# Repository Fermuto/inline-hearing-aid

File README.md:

# inline-hearing-aid
In development.

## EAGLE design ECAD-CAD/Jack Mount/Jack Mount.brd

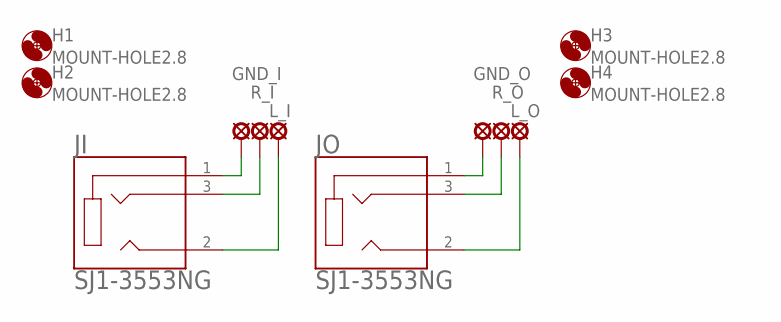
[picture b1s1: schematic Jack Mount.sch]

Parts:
GND_I: LSP10
GND_O: LSP10
H1, H2, H3, H4: MOUNT-HOLE2.8; 2,8
JI: SJ1-3553NG; CUI_SJ1-3553NG
JO: SJ1-3553NG; CUI_SJ1-3553NG
L_I: LSP10
L_O: LSP10
R_I: LSP10
R_O: LSP10

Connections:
unnamed: GND_I.MP, JI.1
unnamed: JI.3, R_I.MP
unnamed: JI.2, L_I.MP
unnamed: GND_O.MP, JO.1
unnamed: JO.3, R_O.MP
unnamed: JO.2, L_O.MP

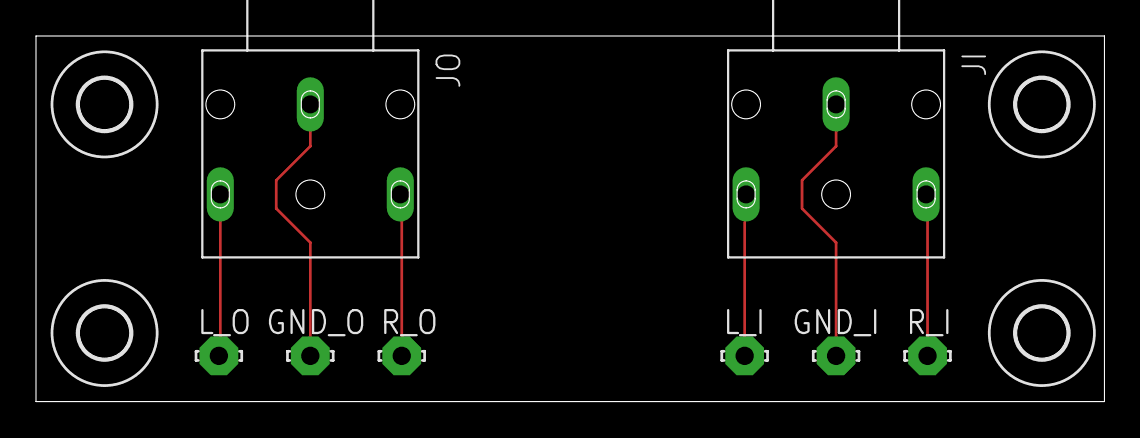
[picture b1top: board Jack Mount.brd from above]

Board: 2 copper layers, 59.4 x 20.3 mm, 12 parts (0 on the bottom side), 6 nets.

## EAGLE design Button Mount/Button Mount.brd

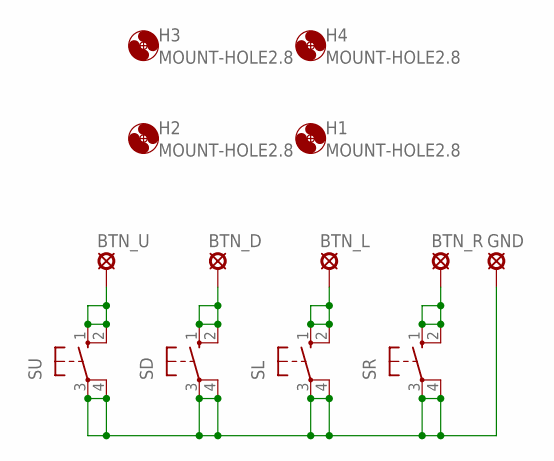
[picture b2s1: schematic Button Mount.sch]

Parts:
BTN_D: LSP10
BTN_L: LSP10
BTN_R: LSP10
BTN_U: LSP10
GND: LSP10
H1, H2, H3, H4: MOUNT-HOLE2.8; 2,8
SD: 10-XX; B3F-10XX
SL: 10-XX; B3F-10XX
SR: 10-XX; B3F-10XX
SU: 10-XX; B3F-10XX

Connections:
unnamed: BTN_U.MP, SU.1 (S), SU.2 (S1)
unnamed: BTN_D.MP, SD.1 (S), SD.2 (S1)
unnamed: GND.MP, SD.3, SD.4 (P1), SL.3, SL.4 (P1), SR.3, SR.4 (P1), SU.3, SU.4 (P1)
unnamed: BTN_L.MP, SL.1 (S), SL.2 (S1)
unnamed: BTN_R.MP, SR.1 (S), SR.2 (S1)

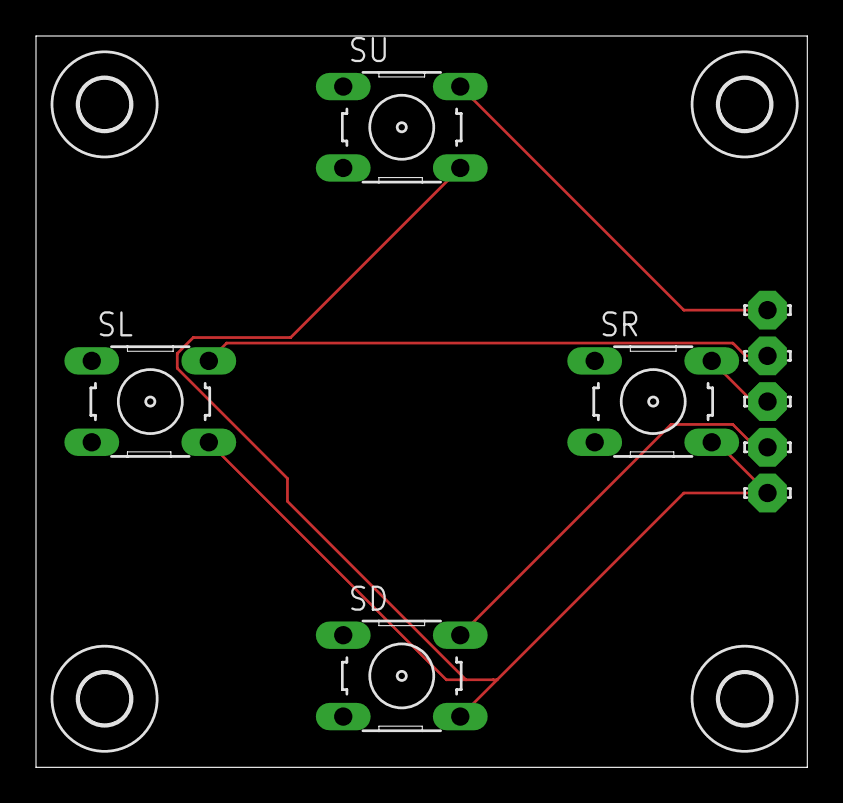
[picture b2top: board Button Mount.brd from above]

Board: 2 copper layers, 42.9 x 40.6 mm, 13 parts (0 on the bottom side), 5 nets.

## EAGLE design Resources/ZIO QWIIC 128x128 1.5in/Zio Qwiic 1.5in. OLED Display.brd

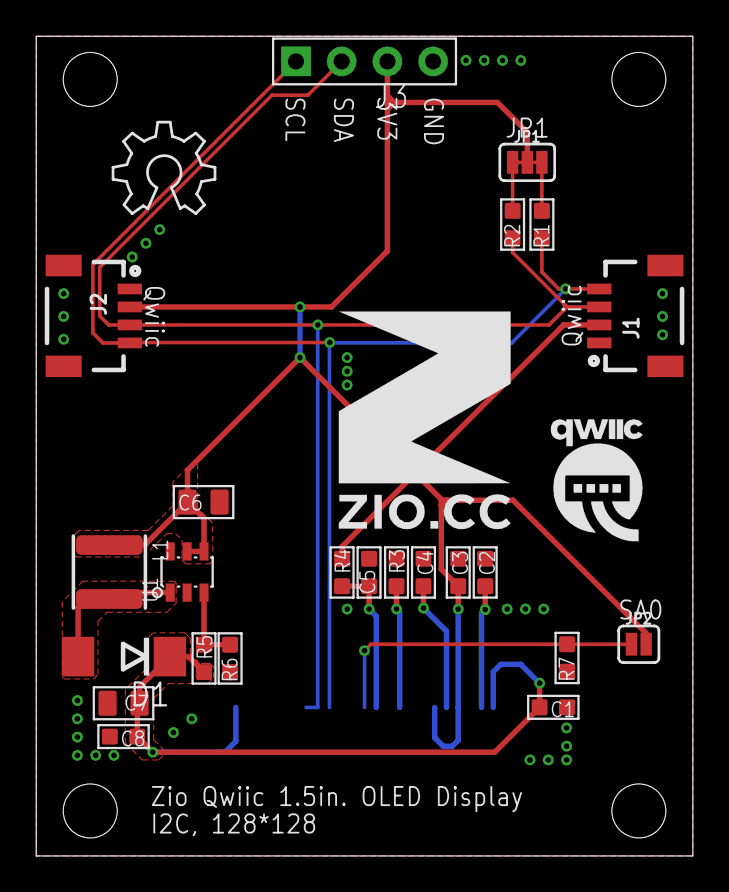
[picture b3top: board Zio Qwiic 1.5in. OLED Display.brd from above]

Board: 2 copper layers, 36.5 x 45.5 mm, 27 parts (1 on the bottom side), 14 nets.

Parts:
C1, C2: 4.7uF ±10% 25V; C0603
C3, C4, C5, C8: 100nF ±10% 50V; C0603
C6, C7: 22uF ±20% 25V; C0805
D1: SS14; DO-214AC
J1, J2: JST-SH-4P-1.0; JST-SH-4P
J3: 4P-65/35MIL
JP1: SMT-JUMPER_3_2-NC_TRACE
JP2: JUMPER-SMT_2_NC_PASTE_NOCREM; SMT-JUMPER_2_NC_PASTE_SILK_NOCREM
L1: PRS4018-4R7MT; L4030
OLED1: OLED_MODULE_1.5IN_128128; OLED_MODULE_1.5IN_128*128
R1, R2: 4.7K ±1%; R0603
R3: 1.2M ±1%; R0603
R4, R6, R7: 10K ±1%; R0603
R5: 240K ±1%; R0603
U1: SX1308; SOT23-6
U$4: 12MM
U$5: QWIIC-LOGO-MEDIUM
U$6: OSHW_6X200_NOTEXT

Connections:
+3V3: C3.2, C6.1, J1.2, J2.2, J3.3, JP1.2, JP2.2, L1.1, OLED1.5, OLED1.7, R4.1, U1.4, U1.5
GND: C1.1, C2.1, C3.1, C4.1, C5.2, C6.2, C7.2, C8.2, J1.1, J1.NC1, J1.NC2, J2.1, J2.NC1, J2.NC2, J3.4, OLED1.1, OLED1.4, OLED1.8, OLED1.9, OLED1.11, OLED1.14, OLED1.15, OLED1.19, OLED1.20, OLED1.21, OLED1.22, OLED1.23, OLED1.25, R3.1, R6.1, R7.1, U1.2
unnamed: JP1.3, R1.2
unnamed: R5.1, R6.2, U1.3
unnamed: JP1.1, R2.2
unnamed: C5.1, OLED1.12, R4.2
unnamed: OLED1.10, R3.2
unnamed: C4.2, OLED1.6
unnamed: C2.2, OLED1.3
SA0: JP2.1, OLED1.13, R7.2
SCL: J1.4, J2.4, J3.1, OLED1.16, R1.1
SDA: J1.3, J2.3, J3.2, OLED1.17, OLED1.18, R2.1
SW: D1.A, L1.2, U1.1
VPP: C1.2, C7.1, C8.1, D1.C, OLED1.2, OLED1.24, R5.2

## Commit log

2022-09-07 Add all boards and schematics
2022-09-07 Restructure folders, add CAD files
    First test of export script
2022-09-07 Second restructure
